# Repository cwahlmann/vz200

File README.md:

# VZ200
## Nachbau eines VZ200-Color-Computers (1983)

Mit einem funktionstüchtigen Nachbau des "VZ200 Color Computer" von 1983 lassen wir die Welt der 8-Bit Computer wieder auferstehen.

__Autoren:__ Jürgen Wahlmann & Christian Wahlmann

Dieses Repository dient der Verwaltung aller Sourcen, insbesondere
* 3d-Modelle (Fusion360)
* Platinenlayout (KiCad)
* Grafiken für Tastatur- und Logo-Aufkleber
* JemuVZ200-Emulator (Java-8 / Gradle)
* VZ200 Companion App (Angular)

Dokumentation und Releases sind gehostet unter https://cwahlmann.github.io/vz200-remake

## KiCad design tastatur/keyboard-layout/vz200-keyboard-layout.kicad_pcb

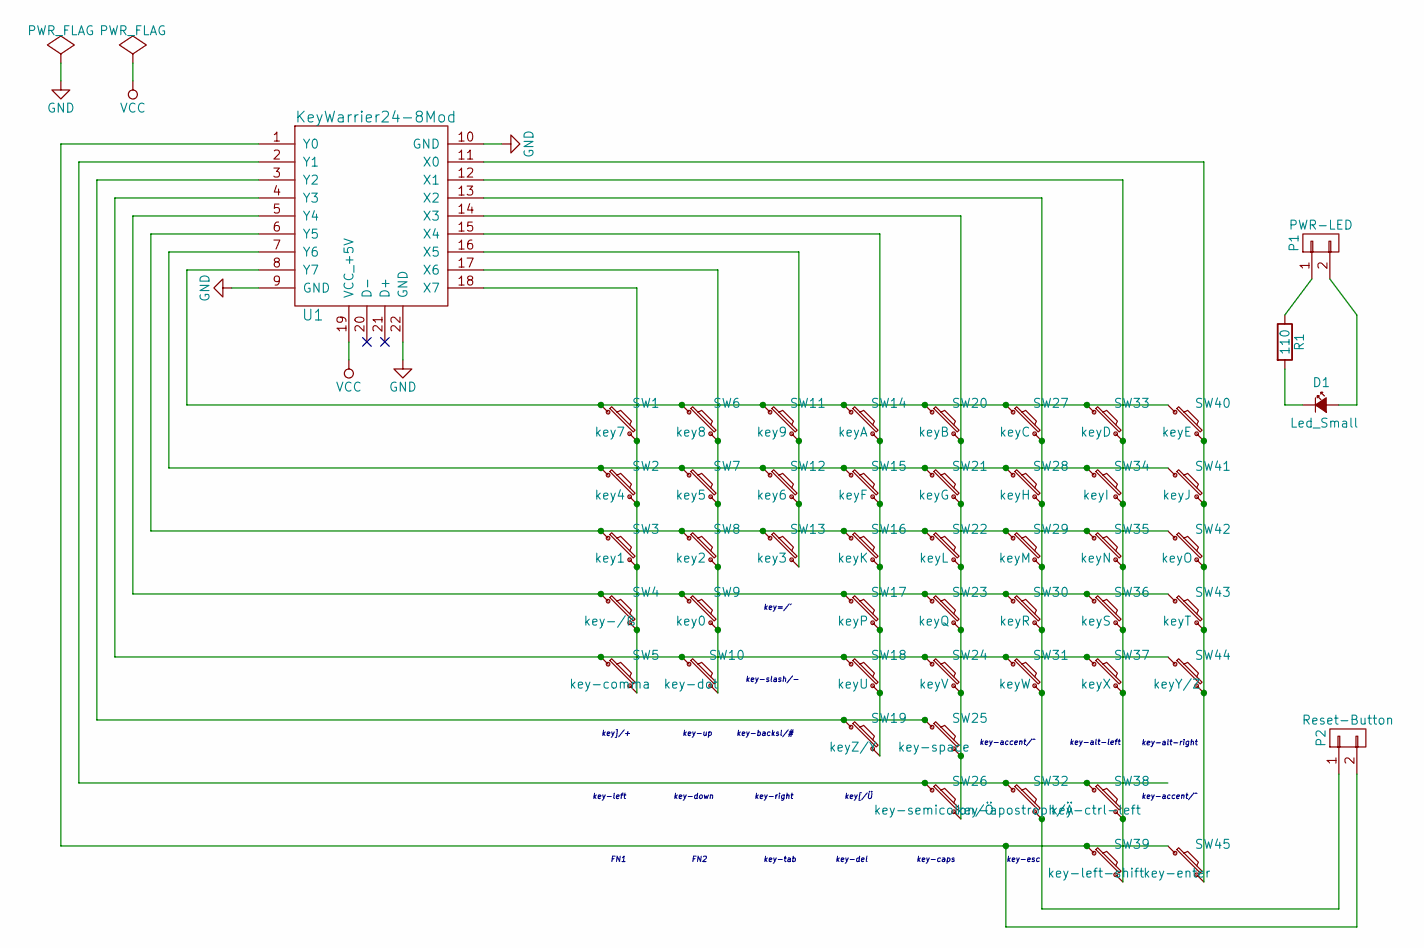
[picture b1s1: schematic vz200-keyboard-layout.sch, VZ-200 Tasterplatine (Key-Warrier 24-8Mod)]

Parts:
D1: Led_Small; LED_D1.8mm_W3.3mm_H2.4mm
P1: PWR-LED; Pin_Header_Straight_1x02_Pitch2.54mm
P2: Reset-Button; Pin_Header_Straight_1x02_Pitch2.54mm
R1: 110; R_Axial_DIN0204_L3.6mm_D1.6mm_P7.62mm_Horizontal
SW1: key7; SW_PUSH_6mm
SW2: key4; SW_PUSH_6mm
SW3: key1; SW_PUSH_6mm
SW4: key-/ß; SW_PUSH_6mm
SW5: key-comma; SW_PUSH_6mm
SW6: key8; SW_PUSH_6mm
SW7: key5; SW_PUSH_6mm
SW8: key2; SW_PUSH_6mm
SW9: key0; SW_PUSH_6mm
SW10: key-dot; SW_PUSH_6mm
SW11: key9; SW_PUSH_6mm
SW12: key6; SW_PUSH_6mm
SW13: key3; SW_PUSH_6mm
SW14: keyA; SW_PUSH_6mm
SW15: keyF; SW_PUSH_6mm
SW16: keyK; SW_PUSH_6mm
SW17: keyP; SW_PUSH_6mm
SW18: keyU; SW_PUSH_6mm
SW19: keyZ/Y; SW_PUSH_6mm
SW20: keyB; SW_PUSH_6mm
SW21: keyG; SW_PUSH_6mm
SW22: keyL; SW_PUSH_6mm
SW23: keyQ; SW_PUSH_6mm
SW24: keyV; SW_PUSH_6mm
SW25: key-space; SW_PUSH_6mm
SW26: key-semicolon/Ö; SW_PUSH_6mm
SW27: keyC; SW_PUSH_6mm
SW28: keyH; SW_PUSH_6mm
SW29: keyM; SW_PUSH_6mm
SW30: keyR; SW_PUSH_6mm
SW31: keyW; SW_PUSH_6mm
SW32: key-apostroph/Ä; SW_PUSH_6mm
SW33: keyD; SW_PUSH_6mm
SW34: keyI; SW_PUSH_6mm
SW35: keyN; SW_PUSH_6mm
SW36: keyS; SW_PUSH_6mm
SW37: keyX; SW_PUSH_6mm
SW38: key-ctrl-left; SW_PUSH_6mm
SW39: key-left-shift; SW_PUSH_6mm
SW40: keyE; SW_PUSH_6mm
SW41: keyJ; SW_PUSH_6mm
SW42: keyO; SW_PUSH_6mm
SW43: keyT; SW_PUSH_6mm
SW44: keyY/Z; SW_PUSH_6mm
SW45: key-enter; SW_PUSH_6mm
U1: KeyWarrier24-8Mod; Socket_Strip_Straight_1x22_Pitch2.54mm

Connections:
GND: U1.9 (GND), U1.10 (GND), U1.22 (GND)
unnamed: D1.1 (K), R1.2
unnamed: D1.2 (A), P1.2
unnamed: P1.1, R1.1
unnamed: P2.1, SW27.2, SW28.2, SW29.2, SW30.2, SW31.2, SW32.2, U1.13 (X2)
unnamed: P2.2, SW39.1, SW45.1, U1.1 (Y0)
unnamed: SW1.1, SW6.1, SW11.1, SW14.1, SW20.1, SW27.1, SW33.1, SW40.1, U1.8 (Y7)
unnamed: SW1.2, SW2.2, SW3.2, SW4.2, SW5.2, U1.18 (X7)
unnamed: SW5.1, SW10.1, SW18.1, SW24.1, SW31.1, SW37.1, SW44.1, U1.4 (Y3)
unnamed: SW6.2, SW7.2, SW8.2, SW9.2, SW10.2, U1.17 (X6)
unnamed: SW11.2, SW12.2, SW13.2, U1.16 (X5)
unnamed: SW2.1, SW7.1, SW12.1, SW15.1, SW21.1, SW28.1, SW34.1, SW41.1, U1.7 (Y6)
unnamed: SW3.1, SW8.1, SW13.1, SW16.1, SW22.1, SW29.1, SW35.1, SW42.1, U1.6 (Y5)
unnamed: SW14.2, SW15.2, SW16.2, SW17.2, SW18.2, SW19.2, U1.15 (X4)
unnamed: SW4.1, SW9.1, SW17.1, SW23.1, SW30.1, SW36.1, SW43.1, U1.5 (Y4)
unnamed: SW19.1, SW25.1, U1.3 (Y2)
unnamed: SW20.2, SW21.2, SW22.2, SW23.2, SW24.2, SW25.2, SW26.2, U1.14 (X3)
unnamed: SW26.1, SW32.1, SW38.1, U1.2 (Y1)
unnamed: SW33.2, SW34.2, SW35.2, SW36.2, SW37.2, SW38.2, SW39.2, U1.12 (X1)
unnamed: SW40.2, SW41.2, SW42.2, SW43.2, SW44.2, SW45.2, U1.11 (X0)
VCC: U1.19 (VCC_+5V)

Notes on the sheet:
key=/´
key-slash/-
key]/+
key-backsl/#
key-accent/^
key-alt-left
key-alt-right
key[/Ü
FN1
FN2
key-tab
key-del
key-caps
key-esc
key-left
key-up
key-down
key-right

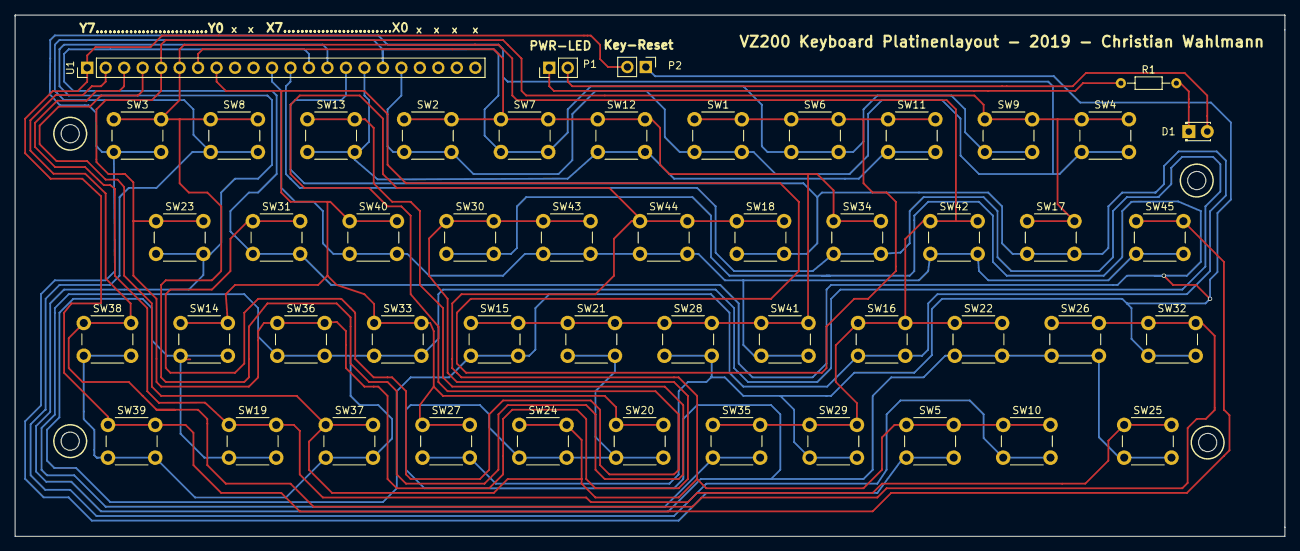
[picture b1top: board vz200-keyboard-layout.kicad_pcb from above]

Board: 2 copper layers, 174.5 x 71.6 mm, 50 parts (0 on the bottom side), 20 nets.

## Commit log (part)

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2019-05-12 emulator: change project name to vz200; change vz-loading, not a write to adress 0 / 1, but OUT to port 252 / 253
2019-05-13 emulator: installation, bug in Rest-Controller
2019-05-13 Ergänzungen
2019-05-17 Update Readme Filamente
2019-05-19 Link zu QEMU raspi Windows Emu hinzugefügt
2019-05-20 emulator: fix another bug in Assembler; HalloWelt2 ist nun ein springender Ball ;-)
2019-05-23 Old TV 3d-Object
2019-05-28 model: logo Textur
2019-06-07 3d-model: Logo VZ200 nachgezeichnet; Tastaturschablone Löcher für Tasten vergrößert
2019-06-11 issue#21: Stutzen für Platinen-Schrauben erstellt
2019-06-17 monitor: Bilder VintageTV verschoben
2019-06-19 Druckinfos
2019-06-20 Tastatur: screenshots und Ordner Tastaturfolie verschoben
2019-06-20 Monitor: Einschub Powerbank entfernt, dafür Lücke für Stromanschluss direkt am TFT (funktioniert besser und man kann zwischen Netzanschluss und Powerbank wählen)
2019-06-25 Tastatur: Screenshots 70% lackiert
2019-06-30 emulator: Rand außerhalb des Bildschirms vergrößert, damit durch Monitorgehäuse keine Zeichen abgeschnitten sind; Rendern der Grafikzeichen gefixt (Bits wurden falsch ausgewertet)
2019-07-01 tastatur /emulator: Reset-Taste (ESC) implementiert; Platinenlayout ergänzt und beschriftet
2019-07-10 3d-modell: Monitor v2.0 finalisiert: mehr Spiel für Schraubstutzen; Lautsprecher eingepasst mit Halterung und Schlitzen; Halterung für Verstärkerplatine; Lüftungsschlitze; Front im Retro-Look
2019-07-22 Emulator: Rest-Endpoint zum Setzen der Audio-Lautstärke hinzugefügt
2019-07-31 emulator: Erweiterung der Rest-Schnittstelle: optionaler autorun-Parameter für POST asm und GET vz; POST asm gibt nun Speicherbereich zurück; thehunter.asm als Minispiel
2019-08-02 Emulator: vz-Start-Script
2019-08-16 Emulator: fix a bug when the VZ is reset; fix the loadAsm-Routine: stop the processor before loading and start it when finished.
2019-08-18 Neuer Druck Gehäuseteil mit RAFT, damit es sauber vom Support getrennt werden kann Fix emulator-Dependencies für Gradle 5.1
2019-09-06 Doku: Images Bauanleitung verkleinert
2019-09-07 Dokumentation: genauere Angaben Bauteile
2019-09-08 Repo bereinigen
2019-09-11 Create README.md
    Short instructions to build and run the app.
2019-09-11 Link auf Companion App Readme hinzugefügt
2019-09-13 doku: Bilder angepasst
2019-09-17 3D-Modell: Texturen für Tastaturschablone und Tasten auf Flächen angebracht; Bilder neu gerendert
2019-09-29 sound: Volume wird nun in Konfigurationsdatei .jemu gesichert; Synchronisationsprobleme bei Sound (Ursache der Knackser) gefixt
2019-10-03 TOM Demo weiterentwickelt
2019-10-27 3D-Modell: Gehäuse oben/unten: 0,5mm Spiel eingebaut, damit die Gehäusehälften besser aufeinander passen
2019-11-02 Gehäuse unten: Resetschalterhalterung um 5mm nach links versetzt Unterseite vorn geglättet für bessere Druckbarkeit Loch für USB-Kabel vergrößert Neue Druckdaten für VZ-Gehäuse
2019-12-07 3D-Modell: Tasten-Aufkleber überarbeitet (fettdruck Funktionstasten); neu: Aufkleber für Gehäuserückseite
2020-01-31 change "hard" reset to soft-reset
2020-02-01 Fix bug in reset routine that causes a delay in sound; remove redundant reset of interruptPending flag (is called in Processor.reset())
2020-02-08 Doku: Monitor Aufbau Bilder
2020-02-08 Dokumentation Monitor Zusammenbau
2020-02-09 REST Service für das Auslesen des Basic-Quellcodes
    Nutzt das Basic-Kommando LLIST und printer.flush().
2020-02-09 Bugfix#74: Rest-Methode zum Export eines Basic-Programms
2020-02-10 Neue REST Methode typetext
    In Arbeit, verschluckt aktuell Sonderzeichen (z.B. ")
2020-02-11 Weiterer Test
    Fehler bei npm ci: Package.json nicht gefunden.
2020-02-11 Material für Basic / Assembler Tutorial (Teil 1)
2020-02-12 Update Angular DevKit
2020-02-12 Coverage added
2020-02-12 Unit Test mit Coverage
2020-02-13 Doku
2020-02-18 z80-Doku kleine Korrekturen
2020-02-22 #71: Implementierung lesen der File Infos; Restcall /vz200/vz/dir
2020-02-23 #71: Beschreibung korrigiert
2020-02-25 #71: Rest-Methoden zum listen / speichern / laden / löschen von VZ-Dateien im VZ-Verzeichnis des Emulators; System.out.println-Loggings entfernt
2020-03-04 #71: add Swagger-UI to Rest-Services
2020-03-15 #71: PC (program-counter)-Änderungen werden nun immer vom Prozessor-Thread selbst durchgeführt; REST-Methode keyboardType cached nun Eingaben und führt sie asynchron durch; unterstützt nun Json; Rese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
2020-03-21 #71: Tapedeck Emulator speichert Tapes nun in einer Datei als JSON
2020-04-07 #80: Unit-Tests; alle REST-Methoden über JWT abgesichert
2020-05-11 #85: README.txt hinzugefügt, diese und Gpl3 werden dem Emulator-Build hinzugefügt.
2020-05-11 #85: Fehler bei Headline gefixt
2020-05-20 #80: REST-Methode für den Download von Screenshots hinzugefügt.
2020-06-01 #91: switch to swagger 3, wich is supported natively be spring boot; fix bug in security device (unused); switch from shadow-jar to boot-jar build; swagger-ui now available at /api/swagger
2020-06-06 #91: new release with fixed vz loader
2020-07-20 Bump lodash from 4.17.15 to 4.17.19 in /apps/VZ200-App
    Bumps [lodash](https://github.com/lodash/lodash) from 4.17.15 to 4.17.19.
    - [Release notes](https://github.com/lodash/lodash/releases)
    - [Commits](https://github.com/lodash/lodash/compare/4.17.15...4.17.19)
2020-09-27 #102: add australian graphics mod; add configuration to enable; add configuration to enable 16k RAM expansion; fix basic cheat sheet; add two hires basic examples
2021-01-04 #104: Device-Scanner; Editor-Theme; Dark/Light-Theme; Banner; App-Icon; Fix some bugs
2021-02-06 #104: Weiterentwicklung der VZ200-UI
2021-03-31 Bump y18n from 4.0.0 to 4.0.1 in /apps/VZ200-App
    Bumps [y18n](https://github.com/yargs/y18n) from 4.0.0 to 4.0.1.
    - [Release notes](https://github.com/yargs/y18n/releases)
    - [Changelog](https://github.com/yargs/y18n/blob/master/CHANGELOG.md)
    - [Commits](https://github.com/yargs/y18n/commits)
2021-05-06 Bump vaadin.version from 14.4.4 to 19.0.6 in /vz200-ui
    Bumps `vaadin.version` from 14.4.4 to 19.0.6.
    Updates `vaadin-bom` from 14.4.4 to 19.0.6
    Updates `vaadin-maven-plugin` from 14.4.4 to 19.0.6
2021-05-09 Bump lodash from 4.17.20 to 4.17.21 in /vz200-ui
    Bumps [lodash](https://github.com/lodash/lodash) from 4.17.20 to 4.17.21.
    - [Release notes](https://github.com/lodash/lodash/releases)
    - [Commits](https://github.com/lodash/lodash/compare/4.17.20...4.17.21)
2021-05-09 Bump elliptic from 6.5.2 to 6.5.4 in /apps/VZ200-App
    Bumps [elliptic](https://github.com/indutny/elliptic) from 6.5.2 to 6.5.4.
    - [Release notes](https://github.com/indutny/elliptic/releases)
    - [Commits](https://github.com/indutny/elliptic/compare/v6.5.2...v6.5.4)
2021-05-29 Bump dns-packet from 1.3.1 to 1.3.4 in /vz200-ui
    Bumps [dns-packet](https://github.com/mafintosh/dns-packet) from 1.3.1 to 1.3.4.
    - [Release notes](https://github.com/mafintosh/dns-packet/releases)
    - [Changelog](https://github.com/mafintosh/dns-packet/blob/master/CHANGELOG.md)
    - [Commits](https://github.com/mafintosh/dns-packet/compare/v1.3.1...v1.3.4)
2021-08-04 Bump tar from 6.0.5 to 6.1.5 in /vz200-ui
    Bumps [tar](https://github.com/npm/node-tar) from 6.0.5 to 6.1.5.
    - [Release notes](https://github.com/npm/node-tar/releases)
    - [Changelog](https://github.com/npm/node-tar/blob/main/CHANGELOG.md)
    - [Commits](https://github.com/npm/node-tar/compare/v6.0.5...v6.1.5)
    ---
    updated-dependencies:
2021-08-30 Bump vaadin-bom from 14.4.4 to 14.6.8 in /vz200-ui
    Bumps vaadin-bom from 14.4.4 to 14.6.8.
    ---
    updated-dependencies:
    - dependency-name: com.vaadin:vaadin-bom
    dependency-type: direct:production
    ...
2021-10-06 Bump url-parse from 1.4.7 to 1.5.3 in /apps/VZ200-App
    Bumps [url-parse](https://github.com/unshiftio/url-parse) from 1.4.7 to 1.5.3.
    - [Release notes](https://github.com/unshiftio/url-parse/releases)
    - [Commits](https://github.com/unshiftio/url-parse/compare/1.4.7...1.5.3)
    ---
    updated-dependencies:
    - dependency-name: url-parse
2022-02-11 Bump karma from 4.1.0 to 6.3.14 in /apps/VZ200-App
    Bumps [karma](https://github.com/karma-runner/karma) from 4.1.0 to 6.3.14.
    - [Release notes](https://github.com/karma-runner/karma/releases)
    - [Changelog](https://github.com/karma-runner/karma/blob/master/CHANGELOG.md)
    - [Commits](https://github.com/karma-runner/karma/compare/v4.1.0...v6.3.14)
    ---
    updated-dependencies:
2022-02-19 Bump url-parse from 1.4.7 to 1.5.7 in /apps/VZ200-App
    Bumps [url-parse](https://github.com/unshiftio/url-parse) from 1.4.7 to 1.5.7.
    - [Release notes](https://github.com/unshiftio/url-parse/releases)
    - [Commits](https://github.com/unshiftio/url-parse/compare/1.4.7...1.5.7)
    ---
    updated-dependencies:
    - dependency-name: url-parse
2022-02-27 Bump url-parse from 1.4.7 to 1.5.10 in /vz200-ui
    Bumps [url-parse](https://github.com/unshiftio/url-parse) from 1.4.7 to 1.5.10.
    - [Release notes](https://github.com/unshiftio/url-parse/releases)
    - [Commits](https://github.com/unshiftio/url-parse/compare/1.4.7...1.5.10)
    ---
    updated-dependencies:
    - dependency-name: url-parse
2022-04-29 Bump async from 2.6.3 to 2.6.4 in /vz200-ui
    Bumps [async](https://github.com/caolan/async) from 2.6.3 to 2.6.4.
    - [Release notes](https://github.com/caolan/async/releases)
    - [Changelog](https://github.com/caolan/async/blob/v2.6.4/CHANGELOG.md)
    - [Commits](https://github.com/caolan/async/compare/v2.6.3...v2.6.4)
    ---
    updated-dependencies:
2022-06-03 Bump @angular/core from 8.1.3 to 11.0.5 in /apps/VZ200-App
    Bumps [@angular/core](https://github.com/angular/angular/tree/HEAD/packages/core) from 8.1.3 to 11.0.5.
    - [Release notes](https://github.com/angular/angular/releases)
    - [Changelog](https://github.com/angular/angular/blob/main/CHANGELOG.md)
    - [Commits](https://github.com/angular/angular/commits/11.0.5/packages/core)
    ---
    updated-dependencies:
2022-10-30 Bump socket.io-parser and karma in /apps/VZ200-App
    Bumps [socket.io-parser](https://github.com/socketio/socket.io-parser) to 4.2.1 and updates ancestor dependency [karma](https://github.com/karma-runner/karma). These dependencies need to be updated t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
    Updates `socket.io-parser` from 3.2.0 to 4.2.1
    - [Release notes](https://github.com/socketio/socket.io-parser/releases)
    - [Changelog](https://github.com/socketio/socket.io-parser/blob/main/CHANGELOG.md)
    - [Commits](https://github.com/socketio/socket.io-parser/compare/3.2.0...4.2.1)
    Updates `karma` from 4.1.0 to 6.4.1
2022-11-19 Bump loader-utils and @angular-devkit/build-angular in /apps/VZ200-App
    Bumps [loader-utils](https://github.com/webpack/loader-utils) to 3.2.1 and updates ancestor dependency [@angular-devkit/build-angular](https://github.com/angular/angular-cli). These dependencies need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
    Updates `loader-utils` from 1.2.3 to 3.2.1
    - [Release notes](https://github.com/webpack/loader-utils/releases)
    - [Changelog](https://github.com/webpack/loader-utils/blob/master/CHANGELOG.md)
    - [Commits](https://github.com/webpack/loader-utils/compare/v1.2.3...v3.2.1)
    Updates `@angular-devkit/build-angular` from 0.803.25 to 15.0.0
2022-12-08 Bump qs and express in /vz200-ui
    Bumps [qs](https://github.com/ljharb/qs) and [express](https://github.com/expressjs/express). These dependencies needed to be updated together.
    Updates `qs` from 6.7.0 to 6.11.0
    - [Release notes](https://github.com/ljharb/qs/releases)
    - [Changelog](https://github.com/ljharb/qs/blob/main/CHANGELOG.md)
    - [Commits](https://github.com/ljharb/qs/compare/v6.7.0...v6.11.0)
    Updates `express` from 4.17.1 to 4.18.2
2022-12-14 Bump express from 4.17.1 to 4.18.2 in /vz200-ui
    Bumps [express](https://github.com/expressjs/express) from 4.17.1 to 4.18.2.
    - [Release notes](https://github.com/expressjs/express/releases)
    - [Changelog](https://github.com/expressjs/express/blob/master/History.md)
    - [Commits](https://github.com/expressjs/express/compare/4.17.1...4.18.2)
    ---
    updated-dependencies:
